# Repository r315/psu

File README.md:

# DPSU

Desk power supply project is intended to develop a compact desk power supply with a dummy load. The power supply can be used to power small devices and perform simple battery capacity test.

---
## Specs

### Power supply

Output: 1.3V - 20V
Output Current: 0A - 1A
Voltage adjustment steps: 100mV
Current adjustment steps: 10mA

### Battery charger

Max charge current: 1A
Battery types: 1S to 4S Li-ion

### Dummy load

Max load: 0.5A
Battery capacity test

---
## Features

* 0.96" Color TFT Screen
* Frontal USB port type A for usb power output
* 1S to 4S Li-ion battery balancer
* Optional supply voltage from internal battery
* Soft power control
* USB serial port available on rear micro usb port type B
* Digital control from tactile keys or serial

---
## Schematics

[Power board](/doc/dpsu_revA_Power_board.PDF)<br>
[Main board](/doc/dpsu_revA_Main_board.PDF)<br>
[Front board](/doc/dpsu_revA_Front_board.PDF)<br>

---
## Images

<div><br></div>

<div><br></div>

<div><br></div>

<div><br></div>

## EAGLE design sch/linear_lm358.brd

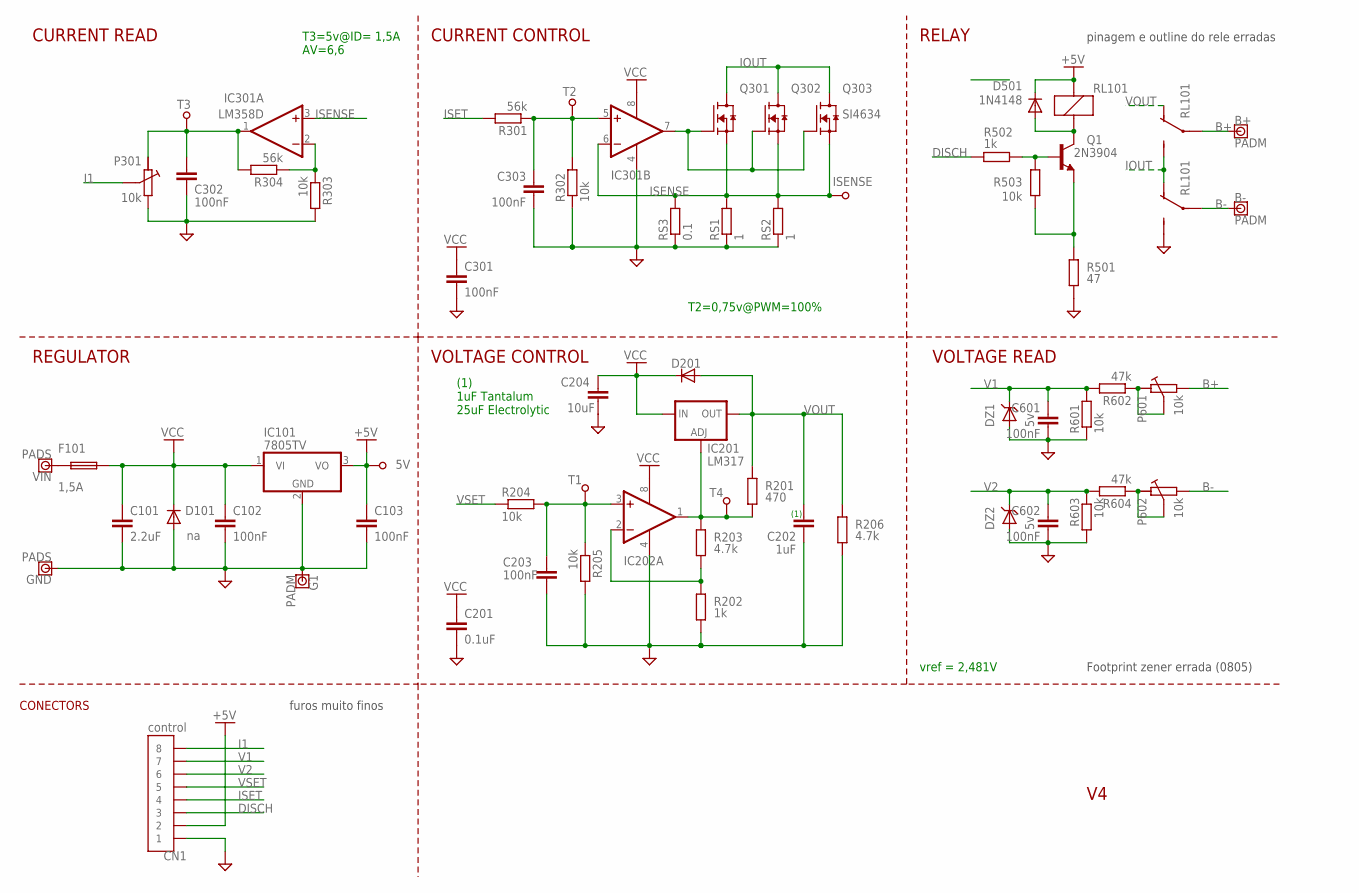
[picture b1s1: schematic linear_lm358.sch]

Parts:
5V: TEST_POINT; TP
B+: PADM; PAD_1M
B-: PADM; PAD_1M
C101: 2.2uF; C3225
C102, C103: 100nF; C3225
C201: 0.1uF; C0805K
C202: 1uF; C1210
C203, C301, C302, C303, C601, C602: 100nF; C0805K
C204: 10uF; C1210
CN1: control; SIL8-0.7
D101, D201: na; DO214BA
D501: 1N4148; DO214BA
DZ1, DZ2: 5v; D0805
F101: 1,5A; F1210L
G1: PADM; PAD_1M
GND: PADS; PAD_01
IC101: 7805TV; TO220V
IC201: LM317; 317TS
IC202, IC301: LM358D; SO08
ISENSE: TEST_POINT; TP
P301, P601, P602: 10k; TRIM_POT
Q1: 2N3904; SOT23
Q301, Q302: AO4468; SO-8
Q303: SI4634; SO-8
R201: 470; M0805
R202: 1k; M0805
R203, R206: 4.7k; M0805
R204, R205, R302, R303, R601, R603: 10k; M0805
R301, R304: 56k; M0805
R501: 47; R0603
R502: 1k; R0603
R503: 10k; R0603
R602, R604: 47k; M0805
RL101: RELAY_351S; 351S
RS1, RS2: 1; 0617/17
RS3: 0.1; R2512
T1, T2, T3, T4: TEST_POINT; TP
VIN: PADS; PAD_01

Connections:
+5V: 5V.1, C103.1, CN1.2, D501.C, IC101.3 (VO), RL101.C1 (1)
B+: B+.1, P601.3, RL101.P1
B-: B-.1, P602.3, RL101.P2
DISCH: CN1.3, R502.2
GND: C101.2, C102.2, C103.2, C201.2, C202.2, C203.2, C204.2, C301.2, C302.1, C303.1, C601.2, C602.2, CN1.1, D101.A, DZ1.A, DZ2.A, G1.1, GND.P, IC101.2 (GND), IC202.4 (V-), IC301.4 (V-), P301.3, R202.2, R205.2, R206.2, R302.1, R303.2, R501.1, R601.1, R603.2, RL101.NO2 (NO), RS1.1, RS2.1, RS3.1
I1: CN1.8, P301.2
IOUT: Q301.5 (D), Q301.6 (D), Q301.7 (D), Q301.8 (D), Q302.5 (D), Q302.6 (D), Q302.7 (D), Q302.8 (D), Q303.5 (D), Q303.6 (D), Q303.7 (D), Q303.8 (D), RL101.NC2 (NC), RL101.NO1 (NO)
ISENSE: IC301.3 (+IN), IC301.6 (-IN), ISENSE.1, Q301.1 (S), Q301.2 (S), Q301.3 (S), Q302.1 (S), Q302.2 (S), Q302.3 (S), Q303.1 (S), Q303.2 (S), Q303.3 (S), RS1.2, RS2.2, RS3.2
ISET: CN1.4, R301.2
unnamed: IC301.7 (OUT), Q301.4 (G), Q302.4 (G), Q303.4 (G)
unnamed: C303.2, IC301.5 (+IN), R301.1, R302.2, T2.1
unnamed: P601.1, P601.2, R602.1
unnamed: IC201.1 (ADJ), IC202.1 (OUT), R201.1, R203.1, T4.1
unnamed: Q1.2 (E), R501.2, R503.2
unnamed: C302.2, IC301.1 (OUT), P301.1, R304.2, T3.1
unnamed: Q1.1 (B), R502.1, R503.1
unnamed: D501.A, Q1.3 (C), RL101.C2 (2)
unnamed: IC301.2 (-IN), R303.1, R304.1
unnamed: IC202.2 (-IN), R202.1, R203.2
unnamed: F101.1, VIN.P
unnamed: P602.1, P602.2, R604.1
unnamed: C203.1, IC202.3 (+IN), R204.2, R205.1, T1.1
V1: C601.1, CN1.7, DZ1.K (C), R601.2, R602.2
V2: C602.1, CN1.6, DZ2.K (C), R603.1, R604.2
VCC: C101.1, C102.1, C201.1, C204.1, C301.1, D101.C, D201.C, F101.2, IC101.1 (VI), IC201.3 (IN), IC202.8 (V+), IC301.8 (V+)
VOUT: C202.1, D201.A, IC201.2 (OUT), R201.2, R206.1, RL101.NC1 (NC)
VSET: CN1.5, R204.1

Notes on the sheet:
(1) 1uF Tantalum 25uF Electrolytic
RELAY
CURRENT CONTROL
VOLTAGE CONTROL
CURRENT READ
VOLTAGE READ
(1)
REGULATOR
CONECTORS
pinagem e outline do rele erradas
furos muito finos
vref = 2,481V
T3=5v@ID= 1,5A AV=6,6
Footprint zener errada (0805)
T2=0,75v@PWM=100%

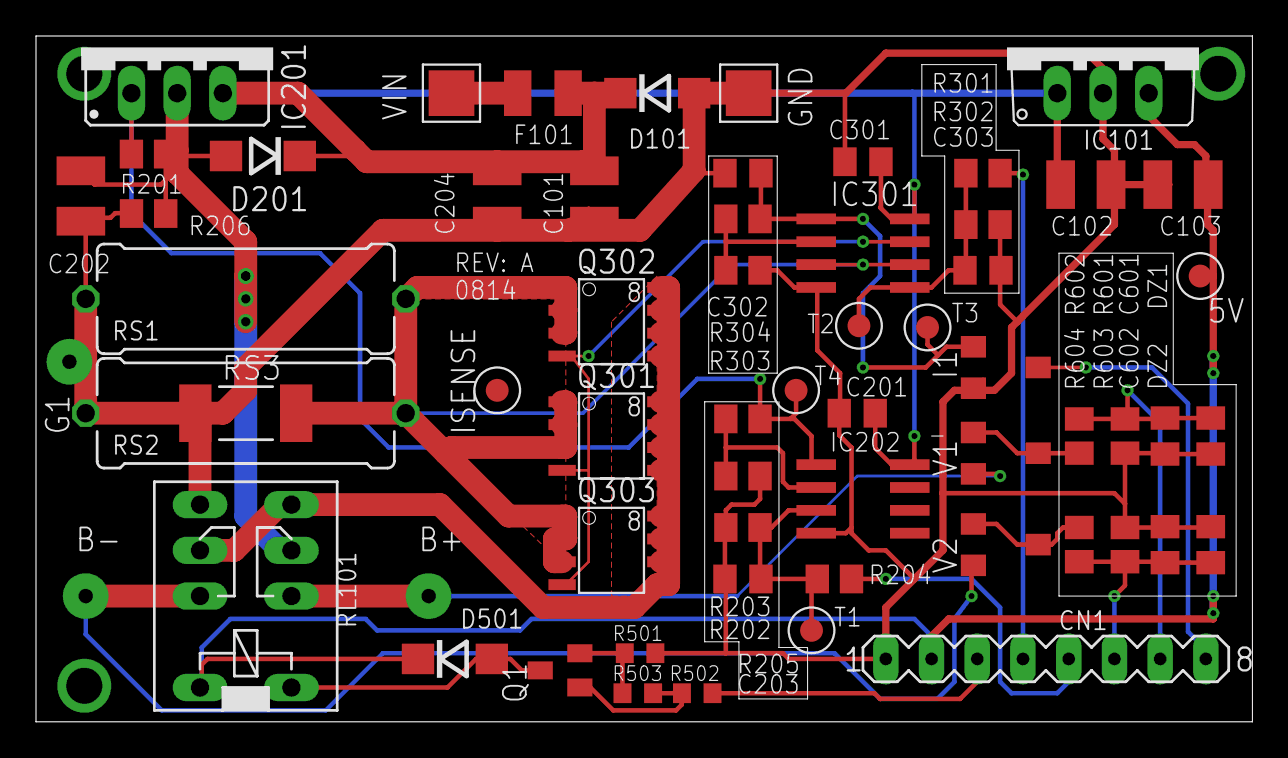
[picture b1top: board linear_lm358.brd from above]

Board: 2 copper layers, 67.6 x 38.1 mm, 62 parts (0 on the bottom side), 27 nets.

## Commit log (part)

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2015-06-10 move to git
2016-08-09 V2.0.0 snapshot
2016-08-10 added features to ps
2016-08-13 initial load function
2016-08-17 change SET icon and working load
2016-08-27 Change Menus and removed string type
    removed string type definition due to not be necessary, menus now support names with different sizes, output is disable on main menu
2016-08-28 Added Rtc changes on gui
    Added timer support for load, gui lay out now is the same for PSU and Load, abandoned graphic idea due to display limitations
2016-08-28 defines renamed changed logic on load and keys functions
    Keys now use function getKey() that returns the key that was pressed and signaled by scanKeys() also this returns pressed key
2018-11-10 Changed project folders
2018-11-10 Added fifo for receiving
2018-11-10 Implemented logic for getting data from fifo
2018-11-10 Updated to match vcom api
2018-11-10 Added command to test path from console to display
2018-11-10 Updated project files
2018-11-10 Fix project build
2018-11-10 Added folder for v2.0
2018-11-10 created folder for project
2018-11-10 Moved v2.0 to pic folder
2018-11-10 Added V1.5
2018-11-10 Added folder for arquitecture
2018-11-10 moved .gitignore and .mxproject
2018-11-10 removed non related folder
2018-11-17 Addec ADC command, made console non blocking
2018-11-18 ADD: Timer, ADC, buttons and board.h
2018-11-18 Revert linker script location
2018-11-20 ADD: ADC configuration
2019-01-05 ADD: psu v3 specific adc driver
2019-01-05 UPD: headers
2019-01-05 ADD: kbhit function, comments
2019-01-05 ADD: pwm driver files
2019-01-06 CHG: ADC Trigger timer to TIM2_CC2 Event
2019-01-06 WIP: pwm
2019-01-06 IMP: PWM api
2019-01-06 ADD: command pwm
2019-02-12 CHG: To console from libemb
2019-02-17 Change compile size output
2019-09-18 updated project directories
2019-09-19 Added dfu submodule
2019-09-21 Integrated DFU feature
2019-09-23 Fixed no image after power cycle
2019-09-23 Added macros
2019-09-24 Add power down command, remove direct calls to I2C driver from lcd driver
2019-09-24 Refactor, make references to fw repository
2019-09-28 added gitattributes
2019-09-28 added generic support for multiple fonts
2019-10-02 Added support for grafic images and fonts
2019-10-02 Normalize all the line endings
2019-10-02 UPD: submodule repository
2019-10-02 WIP: Debug usb not working
2019-10-02 it builds but com port is not started
2019-10-03 Migration to FW 1.8.0
2019-10-03 Added RTOS
2019-10-04 Fix usb reenumeration
2019-10-04 Replaced fifo with queue on vcp
2019-10-04 Created app folder
2019-10-04 Increased heap size
2019-10-04 Added DMA to i2c
2019-10-06 working i2c with dma
2019-10-06 Moved DMA code to board.c, check end of transfer flag on DMA interrupt
2019-10-06 Moved commands to dedicated folder
2019-10-06 Updated button symbols
2019-10-07 Added base screens for operating modes and symbol for dma select
2019-10-09 add i2c io expander driver
2019-10-09 Added logic for user input
2019-10-12 Added comment on pwm
2019-10-12 added space character
2019-10-12 new symbols for pwm
2019-10-12 finished Implementation of psu mode
2019-10-12 fix missing last byte on DMA transfers
2019-10-12 Fix out icon disapear on mode change
2019-10-17 refactor, extracted methods to class
2019-10-19 FIX: adc working with four channels in dual mode
2019-10-19 UPD: debug led macro
2019-10-20 Increaced sampling time.
2019-10-20 moved symbols to class
2019-10-26 moved class out to file, changed prompt to symbol, renamend ConsoleHelp -> CmdHelp
2019-10-26 updated output format
2019-10-26 change debug led macros
2019-10-26 moved hal functions to psu_main
2019-10-26 lcd init check
2019-10-26 REM: text print formated feature
2019-10-26 ADD: calibration data structure
2019-10-26 REN: set_a -> set_i
2019-10-26 IMP: output power update
2019-10-26 ADD: dedicated print functions for power and voltage
2019-10-26 ADD: command to cycle modes
2019-10-26 ADD: bitmaps for unis
2019-10-26 draft ui for load
2019-10-26 ADD: charger mode
2019-10-27 ADD: Icon for charger, renamed field on state
2019-10-27 CHG: remapped PWM and ADC pins
2019-10-27 UPD: specs
2019-10-27 CHG: auto include app source files
2019-10-27 ADD: current print function
2019-10-27 REN: Set modes, initial values for psu mode
2019-10-27 IMP: charger mode ui
2019-11-03 ADD: RTC Api
2019-11-03 Fix: IO expander init
2019-11-03 WIP: UI modes
2019-11-03 UPD: cmd pwm Help
2020-05-20 Change to 80x160 TFT display
    OLED display was better option for laser4+ project
2020-05-20 Changed project folder structure and removed unused code
2020-05-20 added assets folder
2020-05-20 included ioc file
2020-05-20 Moved I2C initialization to board file.
2020-05-23 Changed folder structure
2020-05-23 New module for drawing on the display
2020-05-23 Use draw module
2020-05-23 Renamed functions
2020-05-23 Add 'v' option to pwm command
2020-05-23 Added dual buffer for DMA
2020-05-23 Reduce size of buffers
2020-05-23 Removed TIM hal
2020-06-07 UPD: pwm command
    Now the duty can be set in a single command
2020-06-08 ADD: Adc muc component
2020-06-08 IFDEF for DFU
2020-06-08 REN: functions, added init method to screen class
2020-06-08 ADD: graph class
2020-06-08 Use adc mux
2020-06-08 use graph
2020-06-13 ADD: EEPROM
2020-06-13 FIX: changed typedef
2020-06-13 ADD: debug
2020-06-13 ADD: Command set
2020-06-14 MOV ADCMUX callback to main, changed flags control
2020-06-14 Limit display values
2020-06-14 REM: from compilation unused fonts
2020-06-14 CHG: to xsprintf
2020-06-14 UPD: set command
2020-06-14 ADD: ADC startup calibration
2020-06-22 wip: adc command
2020-06-22 Add missing changes to "Enable option for usb cdc"
2020-06-27 UPD: pwm range value and help
2020-06-28 Change to adc manager Use pin name
2020-06-28 ADD: reset command
2020-07-26 IMP: Serial communication with HW uart
2020-08-05 REM: Startup values for PWM, load default values from eeprom
2020-08-05 ADD: missing changes, comments
2020-08-05 ADD: print all channels values Stop adc manager conversions
2020-08-05 ADD: print pwm values
2020-08-06 CHG: _scratch buffer to static FIX: 8bit inversion on button read
2020-08-06 REN: Variables
2020-08-06 NEW: Status command
2020-08-06 Added missing changes
2020-08-06 MOV: logic to class
2020-08-06 NEW: dummy eeprom data, CHG: screenpreset
2020-08-06 CHG: Reset graph data in init FIX: print out of bound data
2020-08-06 CHG: refactor function names
2020-08-07 CHG: palette to constant
2020-08-07 Filter valid data to be displayed
2020-08-07 ADD: print presetindex
2020-08-07 FIX: SM logic
2020-08-07 Early uart init
2020-08-07 ADD: parameter to cmdset
2020-08-07 ADD: preset index
2020-08-07 ADD: cancel set mode
2020-08-07 REN: screen load file
2020-08-07 FIX: discard set mode when screen is changed
2020-08-13 Added/renamed screen states
2020-08-13 WIP: Screen load state machine
2020-08-14 ADD: Api for dummy load
2020-08-14 CHG: graph size to lcd width
2020-08-14 ADD: macros for text position
2020-10-27 CHG: Use uint32_t insted of float for sotring set values
    Move print functions to base class
2020-10-27 Change pin masks to match HW
    Added macros to control HW
2020-10-27 MXCube project update for 12MHz crystal
2020-10-27 MOV: ADC conversion sequence to adcmgr
2020-10-29 IMP: I2C EEPROM REM: NVDATA
2020-10-31 FIX: EEPROM Write
2020-10-31 IMP: Cmd status
2020-10-31 Added option to break adc manager call loop.
    Implemented cmdadc mgr parameter functions
2020-10-31 CHG: presets, pwm calibration and an channel gains placed on ram
    This change allows loading default values or from EEPROM, this now allows
    erase/set eeprom with default values
2020-10-31 FIX: preset values update
2020-10-31 Enable HW control
2020-11-01 CHG: use indexes intead of pointer for selecting presets
    This allows easier integration with EEPROM
2020-11-01 Access control to I2C peripheral
2020-11-01 Load/save app state
2020-11-05 IMP: watchdog
2020-11-05 CHG: PWM start up values
2020-11-05 IMP: get load voltage and current
2020-11-05 IMP: soft power key
2020-11-05 Files moved
2020-11-05 HW Load set, code refactor
2020-11-06 Code refactor
2020-11-13 IMP: load in Ah unit
2020-11-21 UPD: Backligth pin
2020-11-22 ADD: toggle function for output enable
    Memory allocation fail hook
2020-11-22 Optimized memory allocation
2020-11-23 Changed BUI to MVP pattern
2020-11-24 code refactor/clean
2020-11-24 IMP: psu screen state control
2020-11-29 REM: unused code
2020-11-29 Redraw graph axis on draw
2020-11-29 Added set flags, init, and tick functions
2020-11-29 IMP: task sincronization
2020-11-29 ADD: screen preset
2020-11-29 updated app preset api
2020-11-29 Thread safe call
2020-11-29 Added selection method
2020-11-29 Select screen by index
2020-11-29 Added empty classes for load and charger screens
2020-12-01 new and delete opereator overload
2020-12-01 CHG: screen change through presenter
    presenter now holds pointer to view.
    view will be allocated on presenter.init
2020-12-01 IMP: View and presenter allocation through new operator
2020-12-01 FIX: incorrect index return
2020-12-01 renamed presenter::update presenter::tick
2020-12-04 Updated state machine,
    View is now updated on tick
2020-12-04 Added bui events enum
2020-12-05 Moved icons from app to view
2020-12-05 Move formaters to BUIdro class
2020-12-05 getter for battery pack cell voltage
2020-12-05 IMP: charger screen
2020-12-06 Move costum widgets to common folder
2020-12-06 Cleanup added comments
2020-12-06 Added preset for charging
2020-12-06 New list widget
2020-12-06 wip charge screen
2020-12-06 Optimize state machine
2020-12-06 Removed flags from model
2020-12-10 Disable eeprom with symbol
2020-12-10 Added filter
2020-12-10 Added data model for balancer, reoved flags
2020-12-10 Even more complex state machine
2020-12-10 wip screen charger
2020-12-10 Optimize preset index selection
2020-12-11 REM unused code, implemented set/get adc channle gain
2020-12-11 REM unused code, implemented set/get adc channels gain
2020-12-15 CHG: battery voltage set from pre defined values
2020-12-23 Build UI and CLI as features
2020-12-23 IMP: Charger charge capacity
2020-12-27 Reset capacity with PRE key
2020-12-27 Added redraw method
    This avoids using the flags directlly
2020-12-27 REM: unused symbols
2020-12-27 ADD: variable for load preset
    IMP: get/apply methods
2020-12-27 WIP: Dummy load screen
2021-03-06 CHG: Return accumulated capacity
    Accumulated capacity is computed using parameter insted global variable
2021-03-06 Enable VCOM
2021-03-07 Removed ond ui
2021-03-07 Fill graph empty data with backgound
2021-03-07 Added getter/setter for load preset
2021-03-07 Implemented acccess to editable DRO
2021-03-13 Added buitext for usb current
2021-03-13 ADD: Global convertions counter
2021-03-13 CHG: To timed ADC, improove digital filtering
2021-03-13 MOV: usb source files to lib
2021-03-13 UPD: Default preset values
2021-03-13 ENB: EEPROM
2021-03-13 CHG: Use preset index from app
2021-03-27 IMP: Versioning from git tag
2021-03-27 Code refeactor
2021-03-27 Added documentation
2021-03-27 Filter opamp dead band
2021-03-27 Fill character spacing with backgound color
2021-03-27 Experimets with colors
2021-11-01 CHG: use spi driver
2023-04-26 Updated GPIO configuration
    Moved symbols to tft driver
2023-04-26 Added faoult handlers
2023-04-26 removed unused handler
2023-04-26 Added dma driver
    updated makefile variables
2023-04-26 Added option to disable soft power
2023-04-26 updated commands to console api
2023-04-26 FIX: build for dfu
2025-03-01 WIP: Update to lastest libemb
2025-03-01 CHG: USE_ADCMGR ENABLE_ADC_MGR
2025-03-01 Revert: LD script, the removed sections cause hardfault
2025-03-01 FIX: UART
2025-03-01 CHG: WDT driver
2025-03-01 OPT: To enable ioexpander
2025-03-02 UPD: Dispay defines
2025-03-26 ADD: return value to EEPROM init
2025-03-27 Use logger as debug output
2025-03-27 FIX: Power button
    C6 was populated with an LED, this works as zener diode limiting voltage
    wich now is arround 1.7V
2025-03-27 FIX: build features
2025-03-27 CHG: use io expander component from libemb intead of local
2025-03-27 MOV: EEPROM component to libemb
2025-03-27 FIX: build error
2025-03-27 UPD: eeprom API
2025-04-09 MOV: includes
